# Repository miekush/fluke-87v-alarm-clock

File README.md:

# Fluke 87V Alarm Clock
ATMEGA328P based Alarm Clock PCB for the Fluke 87V

# Documentation

I created a full writeup for this project on Hackster.io. See the project page [HERE](https://www.hackster.io/miekush/fluke-87v-alarm-clock-af6be2)!

Update: Created another writeup for some of the recent upgrades on Hackster.io. See the project page [HERE](https://www.hackster.io/miekush/fluke-87v-alarm-clock-reloaded-a5dd7d)!

# License

MKE supports the open source hardware community by sharing hardware design files freely on GitHub!

Please support MKE by purchasing products on [Tindie](https://www.tindie.com/stores/mkengineering/)!

Designed by Mike Kushnerik (miekush)

Licensed under [Creative Commons Attribution-ShareAlike CC BY-SA 4.0](http://creativecommons.org/licenses/by-sa/4.0/)

All text above must be included in any redistribution!

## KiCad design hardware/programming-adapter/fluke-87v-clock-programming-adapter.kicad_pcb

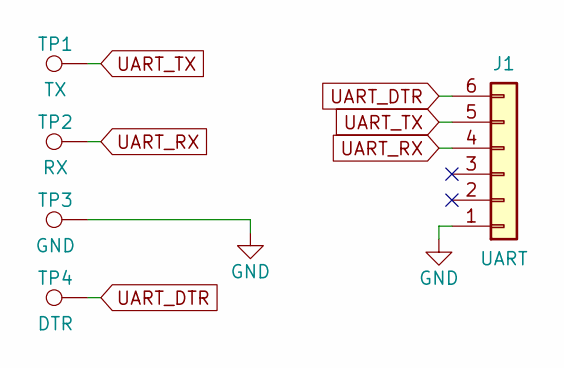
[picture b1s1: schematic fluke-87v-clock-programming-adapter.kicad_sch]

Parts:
J1: UART; PinHeader_1x06_P2.54mm_Vertical
TP1: TX; 4mm_banana_plug
TP2: RX; 4mm_banana_plug
TP3: GND; 4mm_banana_plug
TP4: DTR; 4mm_banana_plug

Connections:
GND: J1.1, TP3.1
UART_DTR: J1.6, TP4.1
UART_RX: J1.4, TP2.1
UART_TX: J1.5, TP1.1

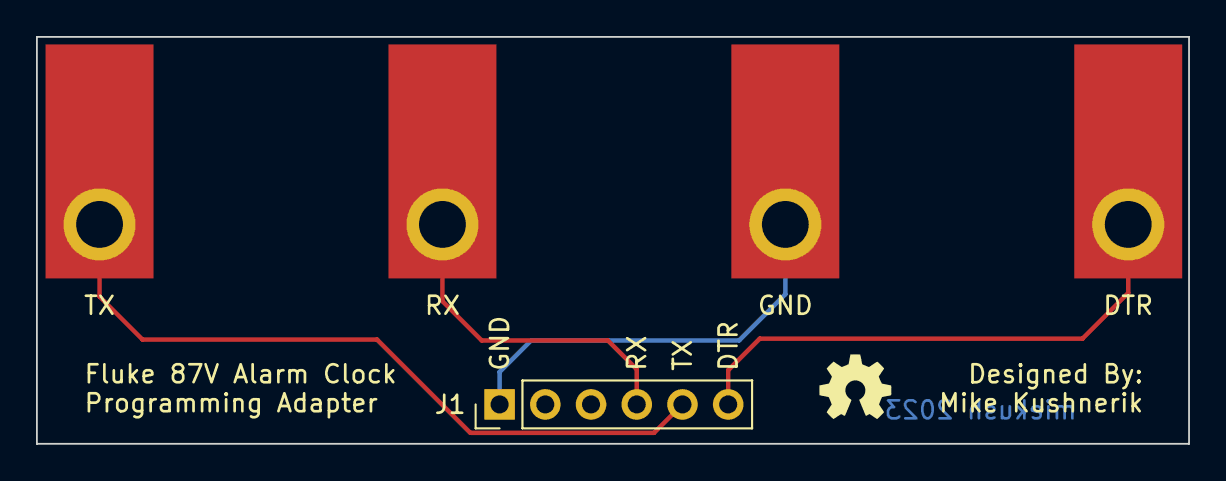
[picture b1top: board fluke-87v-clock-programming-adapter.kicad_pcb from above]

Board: 2 copper layers, 64.0 x 22.6 mm, 5 parts (0 on the bottom side), 4 nets.

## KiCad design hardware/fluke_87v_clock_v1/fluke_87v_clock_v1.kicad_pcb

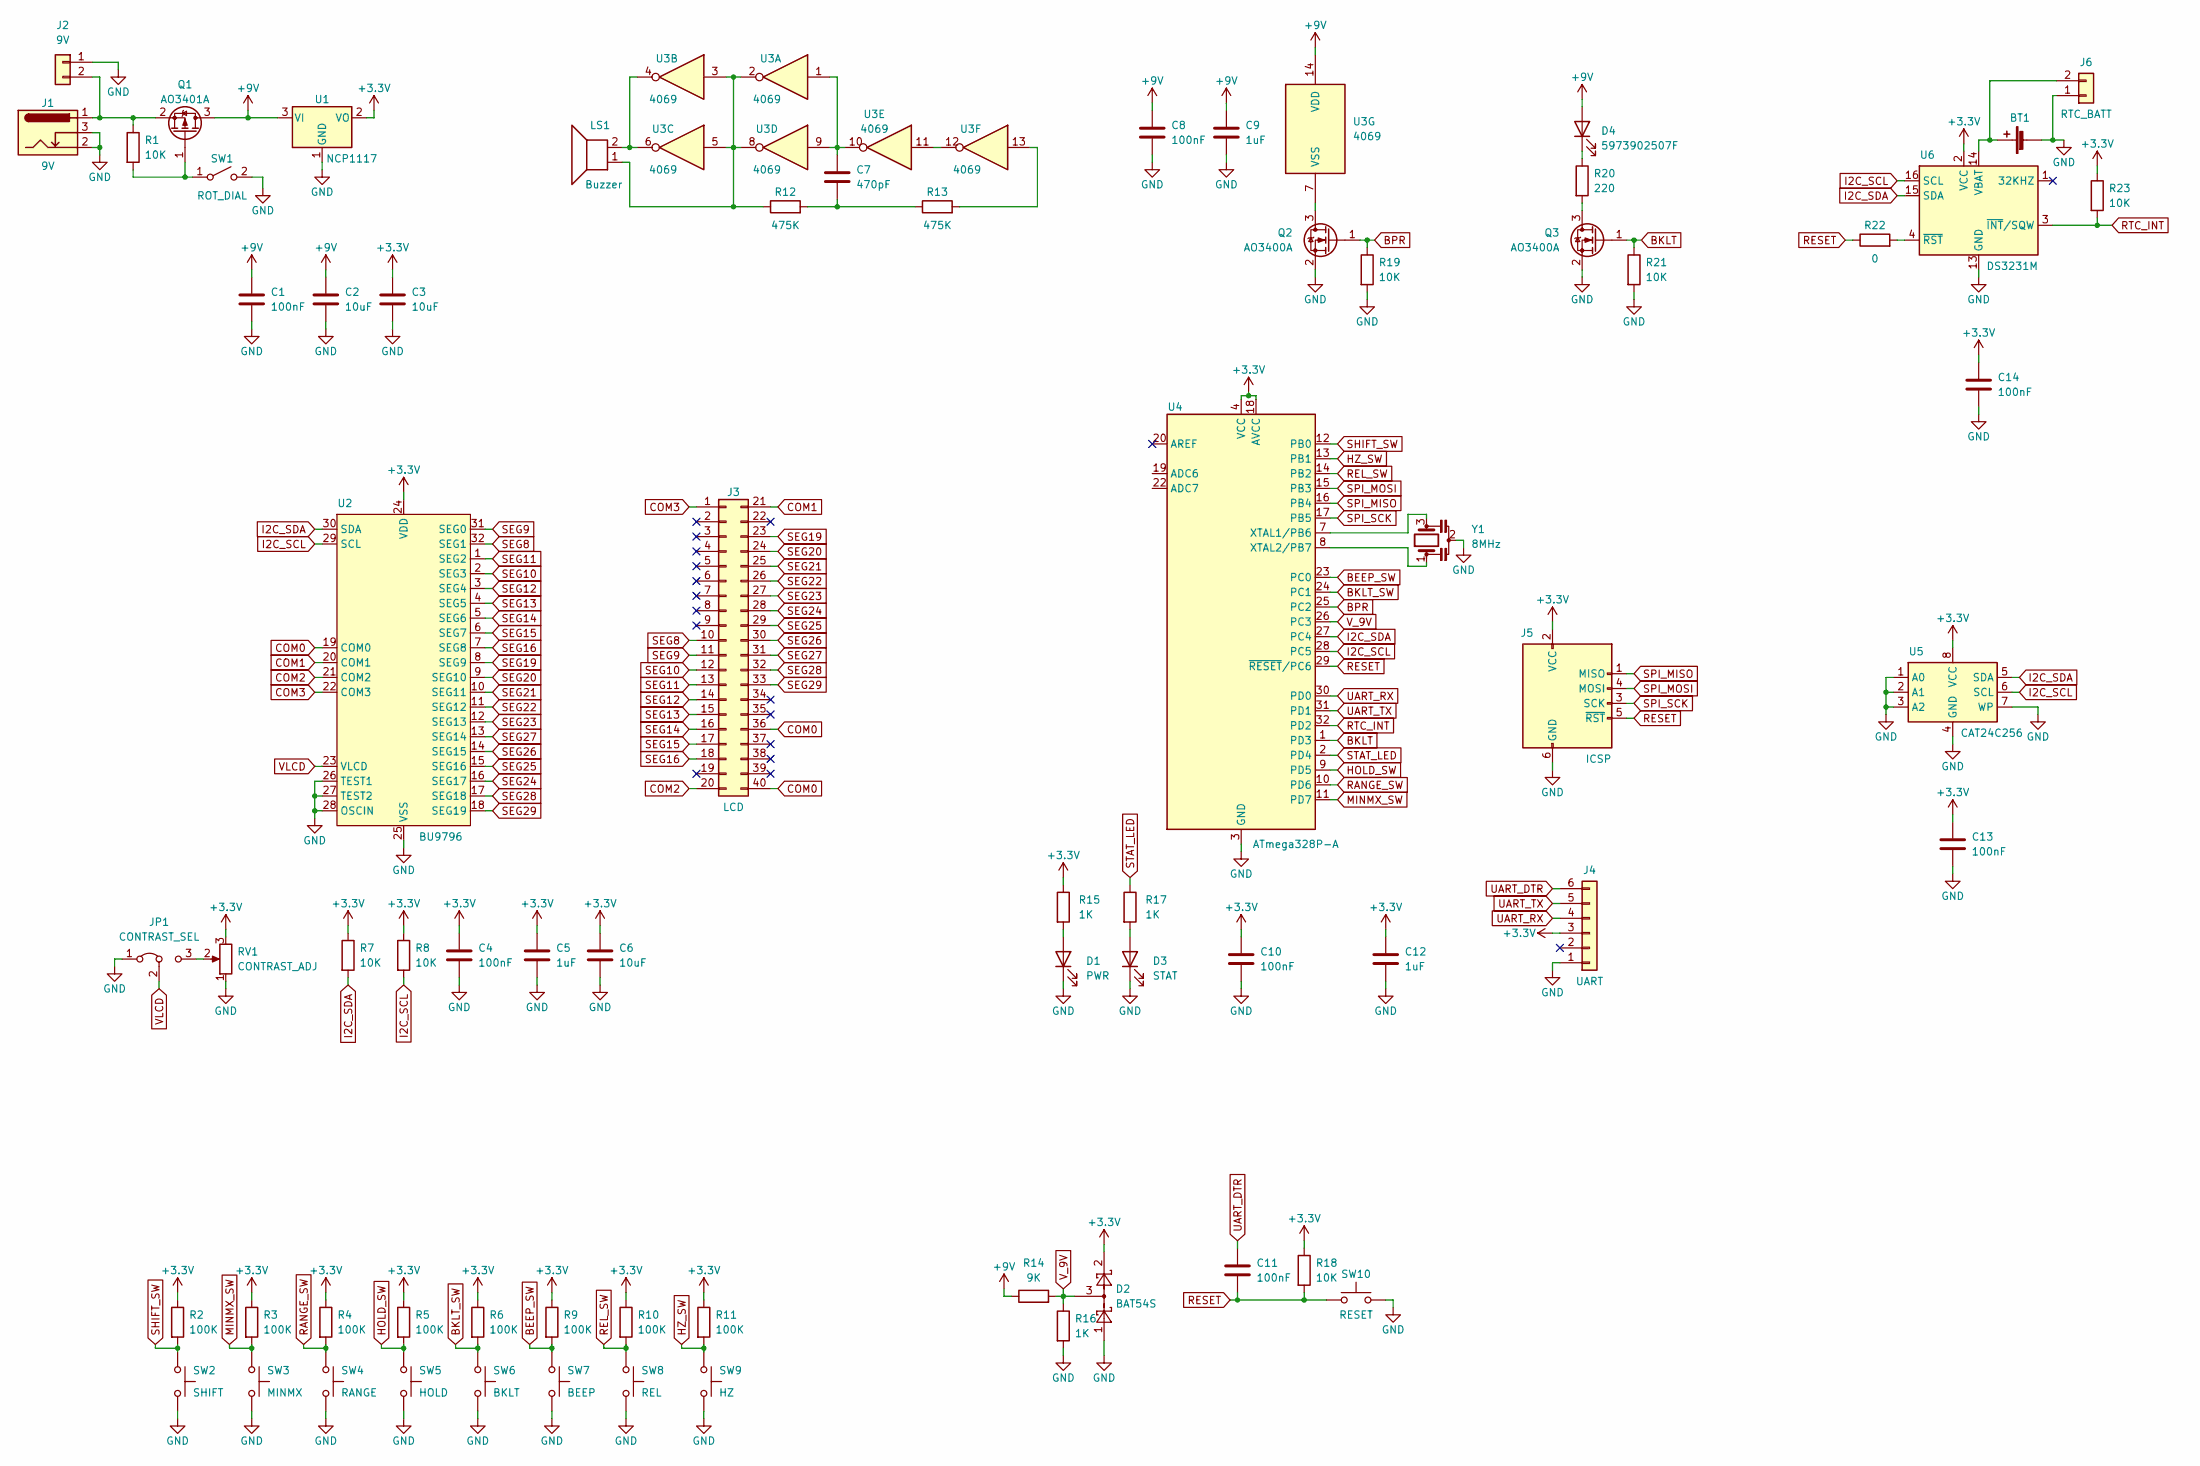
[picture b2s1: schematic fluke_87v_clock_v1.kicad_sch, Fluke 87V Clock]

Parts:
BT1: Battery_Cell; BAT_1056
C1, C4, C8, C10, C11, C13, C14: 100nF; C_0603_1608Metric
C2, C3, C6: 10uF; C_0805_2012Metric
C5, C9, C12: 1uF; C_0603_1608Metric
C7: 470pF; C_0603_1608Metric
D1: PWR; LED_0603_1608Metric
D2: BAT54S; SOT-23
D3: STAT; LED_0603_1608Metric
D4: 5973902507F; LED_3020
J1: 9V; BarrelJack_GCT_DCJ200-10-A_Horizontal
J2: 9V; PinHeader_1x02_P2.54mm_Vertical
J3: LCD; Fluke_87V_LCD
J4: UART; PinHeader_1x06_P2.54mm_Vertical
J5: ICSP; PinHeader_2x03_P2.54mm_Vertical
J6: RTC_BATT; PinHeader_1x02_P2.54mm_Vertical
JP1: CONTRAST_SEL; SolderJumper-3_P1.3mm_Bridged12_Pad1.0x1.5mm
LS1: Buzzer; Fluke_87V_Buzzer
Q1: AO3401A; SOT-23
Q2, Q3: AO3400A; SOT-23
R1, R7, R8, R18, R19, R21, R23: 10K; R_0603_1608Metric
R2, R3, R4, R5, R6, R9, R10, R11: 100K; R_0603_1608Metric
R12, R13: 475K; R_0603_1608Metric
R14: 9K; R_0603_1608Metric
R15, R16, R17: 1K; R_0603_1608Metric
R20: 220; R_0805_2012Metric
R22: 0; R_0603_1608Metric
RV1: CONTRAST_ADJ; Potentiometer_Bourns_TC33X_Vertical
SW1: ROT_DIAL; Fluke_87V_Rotary_Dial
SW2: SHIFT; Fluke_87V_Membrane_SW
SW3: MINMX; Fluke_87V_Membrane_SW
SW4: RANGE; Fluke_87V_Membrane_SW
SW5: HOLD; Fluke_87V_Membrane_SW
SW6: BKLT; Fluke_87V_Membrane_SW
SW7: BEEP; Fluke_87V_Membrane_SW
SW8: REL; Fluke_87V_Membrane_SW
SW9: HZ; Fluke_87V_Membrane_SW
SW10: RESET; SW_PUSH_6mm
U1: NCP1117; SOT-223-3_TabPin2
U2: BU9796; SSOP-A32
U3: 4069; SOIC-14_3.9x8.7mm_P1.27mm
U4: ATmega328P-A; TQFP-32_7x7mm_P0.8mm
U5: CAT24C256; SOIC-8_3.9x4.9mm_P1.27mm
U6: DS3231M; SOIC-16W_7.5x10.3mm_P1.27mm
Y1: 8MHz; Resonator_SMD_Murata_CSTxExxV-3Pin_3.0x1.1mm

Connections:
+3V3: C3.1, C4.1, C5.1, C6.1, C10.1, C12.1, C13.1, C14.1, D2.2, J4.3, J5.2 (VCC), R2.1, R3.1, R4.1, R5.1, R6.1, R7.1, R8.1, R9.1, R10.1, R11.1, R15.1, R18.1, R23.1, RV1.3, U1.2 (VO), U2.24 (VDD), U4.4 (VCC), U4.6 (VCC), U4.18 (AVCC), U5.8 (VCC), U6.2 (VCC)
+9V: C1.1, C2.1, C8.1, C9.1, D4.2 (A), Q1.3 (D), R14.1, U1.3 (VI), U3.14 (VDD)
BEEP_SW: R9.2, SW7.1, U4.23 (PC0)
BKLT: Q3.1 (G), R21.1, U4.1 (PD3)
BKLT_SW: R6.2, SW6.1, U4.24 (PC1)
BPR: Q2.1 (G), R19.1, U4.25 (PC2)
COM0: J3.36, J3.40, U2.19 (COM0)
COM1: J3.21, U2.20 (COM1)
COM2: J3.20, U2.21 (COM2)
COM3: J3.1, U2.22 (COM3)
GND: BT1.2 (-), C1.2, C2.2, C3.2, C4.2, C5.2, C6.2, C8.2, C9.2, C10.2, C12.2, C13.2, C14.2, D1.1 (K), D2.1, D3.1 (K), J1.2, J1.3, J2.1, J4.1, J5.6 (GND), J6.1, JP1.1 (A), Q2.2 (S), Q3.2 (S), R16.2, R19.2, R21.2, RV1.1, SW1.2 (B), SW2.2, SW3.2, SW4.2, SW5.2, SW6.2, SW7.2, SW8.2, SW9.2, SW10.2, U1.1 (GND), U2.25 (VSS), U2.26 (TEST1), U2.27 (TEST2), U2.28 (OSCIN), U4.3 (GND), U4.5 (GND), U4.21 (GND), U5.1 (A0), U5.2 (A1), U5.3 (A2), U5.4 (GND), U5.7 (WP), U6.5 (GND), U6.6 (GND), U6.7 (GND), U6.8 (GND), U6.9 (GND), U6.10 (GND), U6.11 (GND), U6.12 (GND), U6.13 (GND), Y1.2
HOLD_SW: R5.2, SW5.1, U4.9 (PD5)
HZ_SW: R11.2, SW9.1, U4.13 (PB1)
I2C_SCL: R8.2, U2.29 (SCL), U4.28 (PC5), U5.6 (SCL), U6.16 (SCL)
I2C_SDA: R7.2, U2.30 (SDA), U4.27 (PC4), U5.5 (SDA), U6.15 (SDA)
MINMX_SW: R3.2, SW3.1, U4.11 (PD7)
unnamed: BT1.1 (+), J6.2, U6.14 (VBAT)
unnamed: C7.1, U3.1, U3.9, U3.10
unnamed: C7.2, R12.2, R13.1
unnamed: D1.2 (A), R15.2
unnamed: D3.2 (A), R17.2
unnamed: D4.1 (K), R20.1
unnamed: J1.1, J2.2, Q1.2 (S), R1.1
unnamed: JP1.3 (B), RV1.2
unnamed: LS1.1, R12.1, U3.2, U3.3, U3.5, U3.8
unnamed: LS1.2, U3.4, U3.6
unnamed: Q1.1 (G), R1.2, SW1.1 (A)
unnamed: Q2.3 (D), U3.7 (VSS)
unnamed: Q3.3 (D), R20.2
unnamed: R13.2, U3.13
unnamed: R22.2, U6.4 (~RST)
unnamed: U3.11, U3.12
unnamed: U4.7 (XTAL1/PB6), Y1.3
unnamed: U4.8 (XTAL2/PB7), Y1.1
RANGE_SW: R4.2, SW4.1, U4.10 (PD6)
REL_SW: R10.2, SW8.1, U4.14 (PB2)
RESET: C11.2, J5.5 (~RST), R18.2, R22.1, SW10.1, U4.29 (~RESET/PC6)
RTC_INT: R23.2, U4.32 (PD2), U6.3 (~INT/SQW)
SEG8: J3.10, U2.32 (SEG1)
SEG9: J3.11, U2.31 (SEG0)
SEG10: J3.12, U2.2 (SEG3)
SEG11: J3.13, U2.1 (SEG2)
SEG12: J3.14, U2.3 (SEG4)
SEG13: J3.15, U2.4 (SEG5)
SEG14: J3.16, U2.5 (SEG6)
SEG15: J3.17, U2.6 (SEG7)
SEG16: J3.18, U2.7 (SEG8)
SEG19: J3.23, U2.8 (SEG9)
SEG20: J3.24, U2.9 (SEG10)
SEG21: J3.25, U2.10 (SEG11)
SEG22: J3.26, U2.11 (SEG12)
SEG23: J3.27, U2.12 (SEG13)
SEG24: J3.28, U2.16 (SEG17)
SEG25: J3.29, U2.15 (SEG16)
SEG26: J3.30, U2.14 (SEG15)
SEG27: J3.31, U2.13 (SEG14)
SEG28: J3.32, U2.17 (SEG18)
SEG29: J3.33, U2.18 (SEG19)
SHIFT_SW: R2.2, SW2.1, U4.12 (PB0)
SPI_MISO: J5.1 (MISO), U4.16 (PB4)
SPI_MOSI: J5.4 (MOSI), U4.15 (PB3)
SPI_SCK: J5.3 (SCK), U4.17 (PB5)
STAT_LED: R17.1, U4.2 (PD4)
UART_DTR: C11.1, J4.6
UART_RX: J4.4, U4.30 (PD0)
UART_TX: J4.5, U4.31 (PD1)
VLCD: JP1.2 (C), U2.23 (VLCD)
V_9V: D2.3, R14.2, R16.1, U4.26 (PC3)

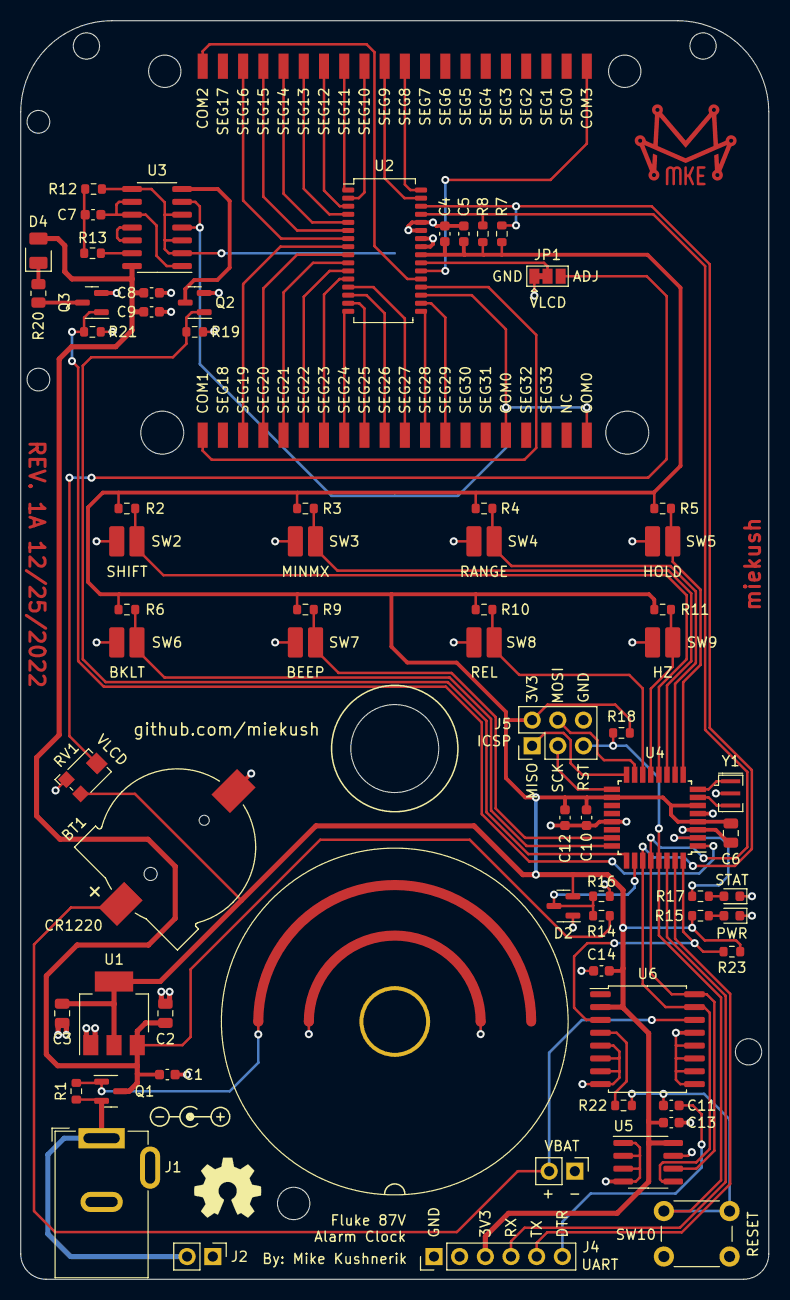
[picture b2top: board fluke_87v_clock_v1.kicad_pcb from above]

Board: 2 copper layers, 74.0 x 124.5 mm, 71 parts (1 on the bottom side), 68 nets.

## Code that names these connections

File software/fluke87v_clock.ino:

#include "bu9796.h"
#include "RTClib.h"
#include "TimerOne.h"

//output pins
#define STAT_LED    4
#define BKLT_PIN    3
#define BZR_PIN     16

//digital input pins 
#define SHIFT_SW    8
#define MINMX_SW    7
#define RANGE_SW    6
#define HOLD_SW     5
#define BKLT_SW     15
#define BEEP_SW     14
#define REL_SW      10
#define HZ_SW       9
#define RTC_INT     2

//analog input pins
#define BAT_V       A3

BU9796 display;
RTC_DS3231 rtc;

bool rtc_interruptFlag = false;
bool prev_bkltSWState = true;
bool current_bkltSWState = true;
bool prev_hold_SWState = true;
bool current_hold_SWState = true;
bool beepFlag = false;
bool holdFlag = false;

void setup()
{
  //init peripheral devices
  display.begin();
  rtc.begin();

  //disable 32 kHz output
  rtc.disable32K();

  //init output pins
  pinMode(STAT_LED, OUTPUT);
  pinMode(BKLT_PIN, OUTPUT);
  pinMode(BZR_PIN, OUTPUT);

  //init input pins
  pinMode(SHIFT_SW, INPUT);
  pinMode(MINMX_SW, INPUT);
  pinMode(RANGE_SW, INPUT);
  pinMode(HOLD_SW, INPUT);
  pinMode(BKLT_SW, INPUT);
  pinMode(BEEP_SW, INPUT);
  pinMode(REL_SW, INPUT);
  pinMode(HZ_SW, INPUT);
  pinMode(RTC_INT, INPUT);

  //turn backlight off by default
  digitalWrite(BKLT_PIN, LOW);

  //turn buzzer off
  digitalWrite(BZR_PIN, LOW);

  //get current state of the backlight switch
  prev_bkltSWState = digitalRead(BKLT_SW);

  //attach interrupt to RTC INT pin
  attachInterrupt(digitalPinToInterrupt(RTC_INT), rtcISR, FALLING);

  //create timer for polling switches
  Timer1.initialize(100000); //100ms
  Timer1.attachInterrupt(pollSwitches);

  //clear alarms
  rtc.clearAlarm(1);
  rtc.clearAlarm(2);

  //turn off squarewave output
  rtc.writeSqwPinMode(DS3231_OFF);

  rtc.setAlarm1(DateTime(2022, 1, 23, 6, 30, 0), DS3231_A1_Hour);

  //configure RTC alarm every minute
  rtc.setAlarm2(rtc.now(), DS3231_A2_PerMinute);

  //write latest rtc time to display
  updateDisplayTime();
}

void loop()
{
  //check for RTC interrupt
  if(rtc_interruptFlag)
  {
    //alarn 1 caused interrupt
    if(rtc.alarmFired(1))
    {
      //clear alarm
      rtc.clearAlarm(2);

      //reset flag
      rtc_interruptFlag = false;

      //get latest time from RTC and write to display
      updateDisplayTime();

      //blink display segments (1 Hz)
      display.blink(1000);

      //alarm loop until reset
      while(1)
      {
        toggleBacklight();
        buzzerBeep(1000);
        toggleBacklight();
        delay(1000);
      }
    }
    //alarm 2 caused interrupt
    else
    {
      //clear alarm
      rtc.clearAlarm(2);

      //get latest time from RTC and write to display
      updateDisplayTime();

      //reset flag
      rtc_interruptFlag = false;      
    }
  }

  //check for single beep request (i.e. button press)
  if(beepFlag)
  {
    buzzerBeep(100);
    beepFlag = false;
  }

  if(holdFlag)
  {
    displayBatteryVoltage();
    delay(500);
  }
}

void rtcISR()
{
  rtc_interruptFlag = true;
}

void updateDisplayTime(void)
{
  //get latest time from RTC
  DateTime now = rtc.now();

  //write time to display
  display.writeValue((now.twelveHour() * 100) + now.minute());
  display.setDecimalPoint(3);
  display.update();
}

void displayBatteryVoltage(void)
{
  //read battery voltage
  int battV = 10.1 * (3300.0 * (analogRead(BAT_V) / 1023.0));
  display.writeValue(battV);
  display.update();
}

void pollSwitches(void)
{
  //read current switch status
  current_bkltSWState = digitalRead(BKLT_SW);
  current_hold_SWState = digitalRead(SHIFT_SW);

  //falling edge
  if(current_bkltSWState == LOW && prev_bkltSWState == HIGH)
  {
    toggleBacklight();
    beepFlag = true;
  }

  //falling edge
  if(current_hold_SWState == LOW && prev_hold_SWState == HIGH)
  {
    holdFlag = true;
  }
  //rising edge
  else if(current_hold_SWState == HIGH && prev_hold_SWState == LOW)
  {
    holdFlag = false;
    rtc_interruptFlag = true;
  }

  prev_bkltSWState = current_bkltSWState;
  prev_hold_SWState = current_hold_SWState;
}

void toggleBacklight(void)
{
  //toggle bklt pin
  digitalWrite(BKLT_PIN, !digitalRead(BKLT_PIN));
}

void buzzerBeep(int ms)
{
  digitalWrite(BZR_PIN, HIGH);
  delay(ms);
  digitalWrite(BZR_PIN, LOW);
}

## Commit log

2023-01-29 Initial upload
2023-09-30 Update files
